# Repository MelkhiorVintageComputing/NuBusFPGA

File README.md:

# A FPGA on a NuBus card...

## Goal

The goal of this repository is to be able to interface a modern (2021 era) [FPGA](https://en.wikipedia.org/wiki/Field-programmable_gate_array) with a [NuBus](https://en.wikipedia.org/wiki/NuBus) host, specifically Apple's [Macintosh II](https://en.wikipedia.org/wiki/Macintosh_II_family) and [Macintosh Quadra](https://en.wikipedia.org/wiki/Macintosh_Quadra). NuBus was widely used by Apple and a little by others (such as NeXT), but was progressively displaced by PCI from the mid-90s onward, and is thoroughly obsolete.

So unless you're a retrocomputing enthusiast with such a machine, this is useless. If you are such an enthusiast, then maybe the ability to connect a modern LCD monitor using a digital interface to an old Macintosh might be of interest to you.

This project was 'spun off' the [SBusFPGA](https://github.com/rdolbeau/SBusFPGA), a similar project for the SBus used in Sun's SPARCstation.

## Current status

First prototype is working in a Quadra 650, running MacOS 8.1. It implements a single-screen-resolution, windowboxed multi-resolution, depth-switchable (1/2/4/8/16/32 bits) framebuffer over DVI-in-HDMI-connector (will work with any HDMI-compliant monitor). The framebuffer can be used as secondary/primary/only framebuffer in the machine running OS8.1. Qemu tests indicate this should work with 7.1 & 7.5/7.6 as well. An alternate HDMI PHY also supports audio, enabled as a 8/16 bits, mono/stereo, 44.1 kHz output component in MacOS.

Some basic acceleration now exists for 8/16/32 bits, doing rectangle screen-to-screen blits and pattern rectangle fills. 1/2/4 bits also has some acceleration, but only for byte-aligned cases.

There's also a basic RAM Disk using the 248 MiB of SDRAM not used by the framebuffer. The driver can use either synchronous direct access to the memory by the CPU, or asynchronous using DMA (using 16-bytes blocks). Frustratingly, the direct access methode seems faster.

## The hardware

Directory 'nubus-to-ztex'

The (now obsolete) V1.0 custom board is a NuBus-compliant (I hope...) board, designed to receive a [ZTex USB-FPGA Module 2.13](https://www.ztex.de/usb-fpga-2/usb-fpga-2.13.e.html) as a daughterboard. The ZTex module contains the actual FPGA (Artix-7), some RAM, programming hardware, etc. The NuBus board contains level-shifters & drivers ICs to interface between the NuBus signals and the FPGA, a CPLD handling some level-shifting & the bus mastering arbitration, a serial header, two user Leds, 14 debug Leds tied to specific NuBus or CPLD/FPGA signals, a JTAG header, a USB micro-B connector, a VGA chip & connector, and a HDMI chip & connector. It supports every NuBus feature except the optional parity (i.e. it can do both slave and master modes). The V1.0 board is in commit 3f3371a. The CPLD solution works but is annoying as it requires older Xilinx software (ISE 14.7) and dedicated JTAG programmer to use.

The current board is V1.2. It drops the CPLD and VGA port. Bus arbitration is now done inside the FPGA. It gains a micro-sd slot, and a custom expansion connector that is based (and compatible with, with more signals) PMod. It supports the same accelerated HDMI framebuffer and RAM Disk. Optionally, The Declaration Rom can be stored in a Flash NOR chip connected ot the PMOd expansion connector (easier for working on embedded driver in the DeclRom). The ROM can alternately be stored in a sector of the config flash from the ZTex board on any *FPGA.

The new (July 2023) [ZTex USB-FPGA Module 2.12](https://www.ztex.de/usb-fpga-2/usb-fpga-2.12.e.html) is theoretically compatible with all *FPGA, but at this stage there is some issue when using the 2.12b I own. Some further tests are planned.

The PCBs were designed with Kicad 5.1

## The gateware (Migen)

Directory 'sbus-to-ztex-gateware'

The gateware is written in the Migen language, choosen because that's what [Litex](https://github.com/enjoy-digital/litex/) uses.
It implements a simple CPU-less Litex SoC built around a Wishbone bus, with a custom bridge between the NuBus and the Wishbone.

A Declaration ROM, a SDRAM controller ([litedram](https://github.com/enjoy-digital/litedram) to the on-board DDR3), and the 'Goblin' multi-depth framebuffer can be connected to that bus. Other devices could be added, see the SBusFPGA or the [Common](https://github.com/rdolbeau/VintageBusFPGA_Common) directory, but the software support is missing; vintage System 7/MacOS 8 are not as welcoming to new devices as modern NetBSD. Theoretically, quite a bit of code originally written to support the SBusFPGA in NetBSD/sparc could be reused for similar devices in NetBSD/mac68k, but it has not happened yet.

The SDRAM has its own custom DMA controller, using native Litedram interface to the memory, and some FIFO to/from the NuBus. A custom MacOS driver exposes it as a volatile drive. Driver can use synchronous direct accesses from the CPU (using the NuBus's superslot area), or asynchronous (interrupt-driven) DMA transfers using NuBus 1x block transfers.

## The software

The Declaration ROM is in the subdirectory VintageBusFPGA_Common/DeclROM and includes the driver needed for the unaccelerated framebuffer and the RAM Disk. It needs the [Retro68](https://github.com/autc04/Retro68) toolchain to build.

The code for the NuBusFPGAInit (which should be renamed and enables acceleration) is in NuBusFPGAInit/, and will need a CodeWarrior INIT project to build, on a real Macintosh or an emulated one using e.g. Qemu. It enables graphic acceleration.

The code for the Audio component (which enables audio support over HDMI when using the alternate PHY) is in NuBusFPGAHDMIAudio/.

## FAQ

* Can the framebuffer change resolution ?
 Yes and no. The gateware has a default resolution baked into it that the device will use by default, and can use one of two different physical interface (PHY): the Litex-derived one (which uses DVI signalling) or a more HDMI-like one in verilog. "windowboxed" mode is always availeble, where a smaller esolution is displayed in the middle of the larger screen, which you can select in System 7/MacOS 8 with the Monitor control panel. When using the Litex PHY, some resolution are also available as "hardware" resolution, outputing the appropriate signalling - but the Litex PHY doesn't support audio. The alternate PHY does support audio, but doesn't allow to use a different output resolution, only Full HD (1920x1080) and does support audio output.

* Is Audio supported ?
 Yes and no. a 8 or 16-bits, audio or stereo, 44.1 KHz audio device is available but nly when using the alternate HDMI PHY (see previous question)

* Is USB supported ?
 No. There is a USB connector, but it is currently useless. The gateware could include a USB OHCI host device, and that is supported in the SBusFPGA under NetBSD. However, no Apple OS running on a 68k Mac has any support for USB, so it would require an entire USB stack to be ported, which is a huge undertaking. Also, NuBus is quite a slow bus even by early 2000s standard, and USB OHCI does a lot of DMA all the time, which would use up most if not all (or maybe more than all!) the available bandwidth. There might be some support in NetBSD/mac68k eventually just to test feasibility, but it even there it's unlikely to be useful.

* Is micro-sd supported ?
 Not yet. Hopefully at some point the micro-sd card will be usable as permanent storage in System 7/MacOS 8, but so far it's not working.

* Where is the ROM stored ?
 By default the Declaration ROM is stored inside the FPGA bitstream, so the bitstream must be regenerated for every ROM change. It is possible to store it in a [SPI](https://en.wikipedia.org/wiki/Serial_Peripheral_Interface) Flash NOR chip instead, connected via the expansion connector ([PMod](https://digilent.com/reference/pmod/start)-like) at the back of the NuBusFPGA. My own PMod featuring a SPI Flash NOR and an I2C temperature monitoris available in the [VintageBusFPGA_Common](https://github.com/rdolbeau/VintageBusFPGA_Common) repository, along with an adapter board to program the SPI FLash NOR through the SPI interface of a Raspberry Pi and [flashrom](https://www.flashrom.org/Flashrom).

* Is I2C supported ?
 No. Like USB, I2C doesn't have support in System 7/MacOS 8. It's a lot simpler than USB though. Reading values from a lm75-compatible temperature monitor from System 7/MacOS 8 might be doable, but isn't currently planned. Support for NetBSD/mac68k should be reasonably easy to add as it's already supported in NetBSD/sparc for the SBusFPGA, and unlike USB there's no issue with bandwidth-hungry DMA.

* How about adding Ethernet ?
 Software is the issue. Ethernet is supported by the gateware infrastructure, and a prototype design to add Fast Ethernet via RMII through the expansion connector is available. However, there is currently no software support for it. There's some documentation from Apple, and there's [an example driver available](http://www.mactcp.org.nz/ethernet.html), but the System 7/MacOS 8 driver for LiteEth is still to be written.
 The [SEthernet](https://github.com/rhalkyard/SEthernet) project is a much more likely source of Ethernet for '030-based system.

* Why slow NuBus, when PDS is so much faster ?
 NuBus is well documented, and electrically quite isolated from the rest of the machine. Safer to play with than PDS which is directly connected to the CPU. And the connector for it it still in general use and easy to get. And NuBus is available on multiple generations of machines.
 My primary machine for this is a Quadra 650, with a 68040 and the associated PDS. Unfortunately, the connector for that PDS is near impossible to get nowadadays ([specifications are there](https://tinkerdifferent.com/resources/specifications-for-the-quadra-pds-connector.124/)). '030 PDS uses 120-pins DIN 41612, similar to bur larger than NuBus' 96-pins. They are also available, but less common. But there is a catch - although sharing a connector board-side, the IIsi, SE/30 and IIfx pinouts are slightly different. And the LCIII is completely different.
 Also - see [IIsiFPGA](https://github.com/rdolbeau/IIsiFPGA) and [QuadraFPGA](https://github.com/rdolbeau/QuadraFPGA) :-)

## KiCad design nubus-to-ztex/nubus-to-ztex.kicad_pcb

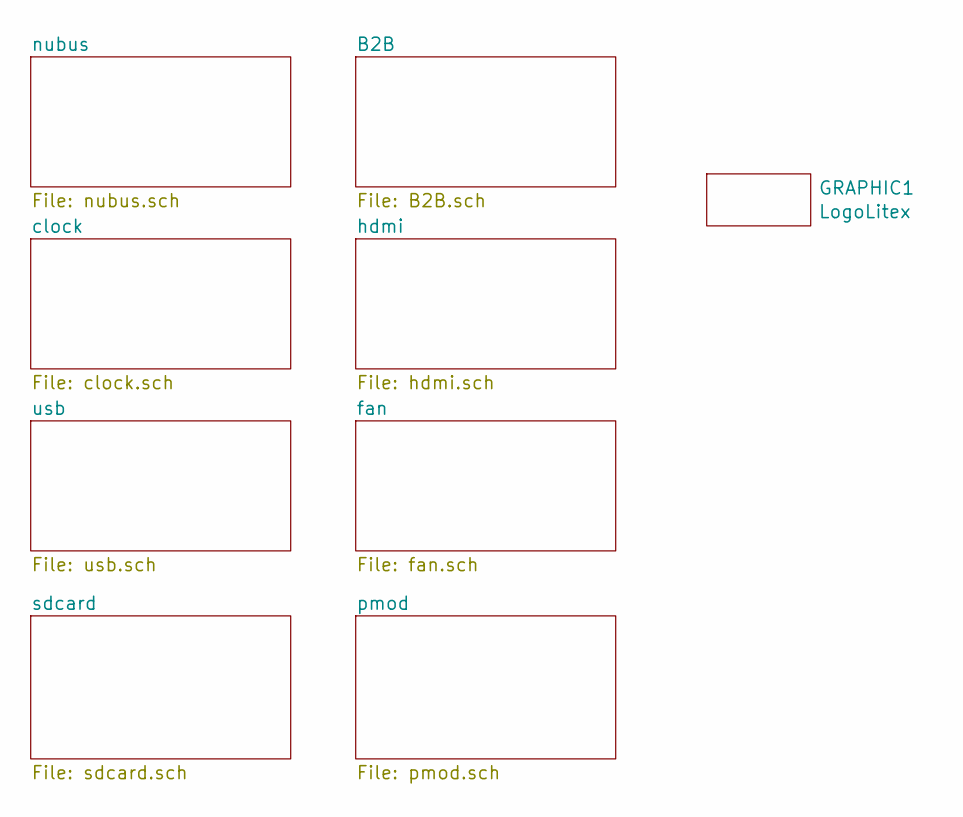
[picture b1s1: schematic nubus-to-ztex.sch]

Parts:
GRAPHIC1: LogoLitex; litex_logo

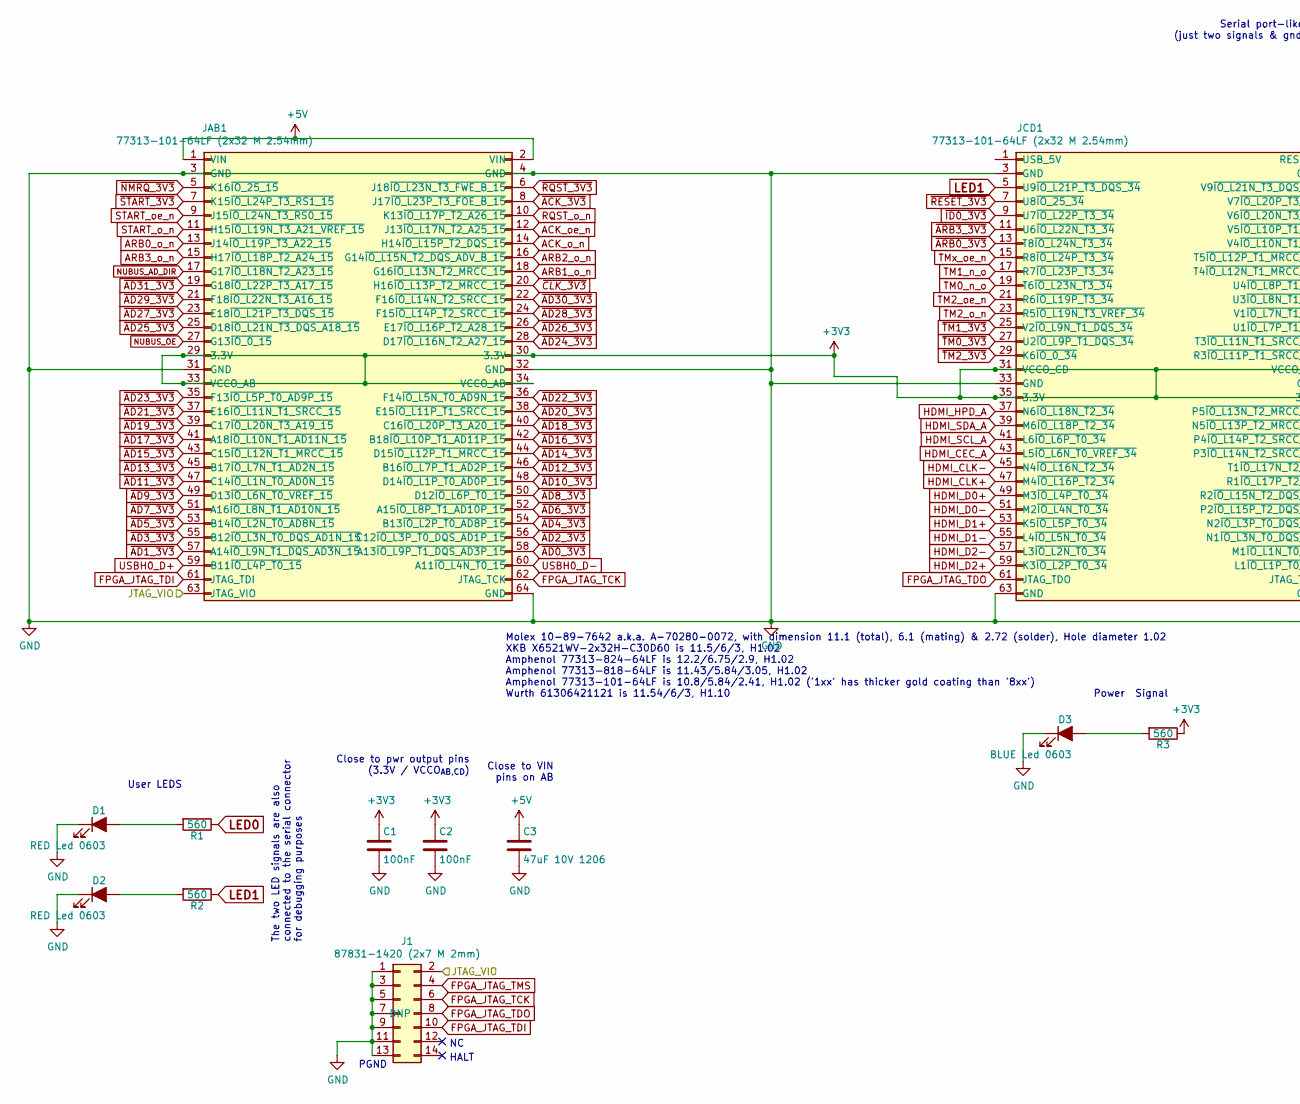
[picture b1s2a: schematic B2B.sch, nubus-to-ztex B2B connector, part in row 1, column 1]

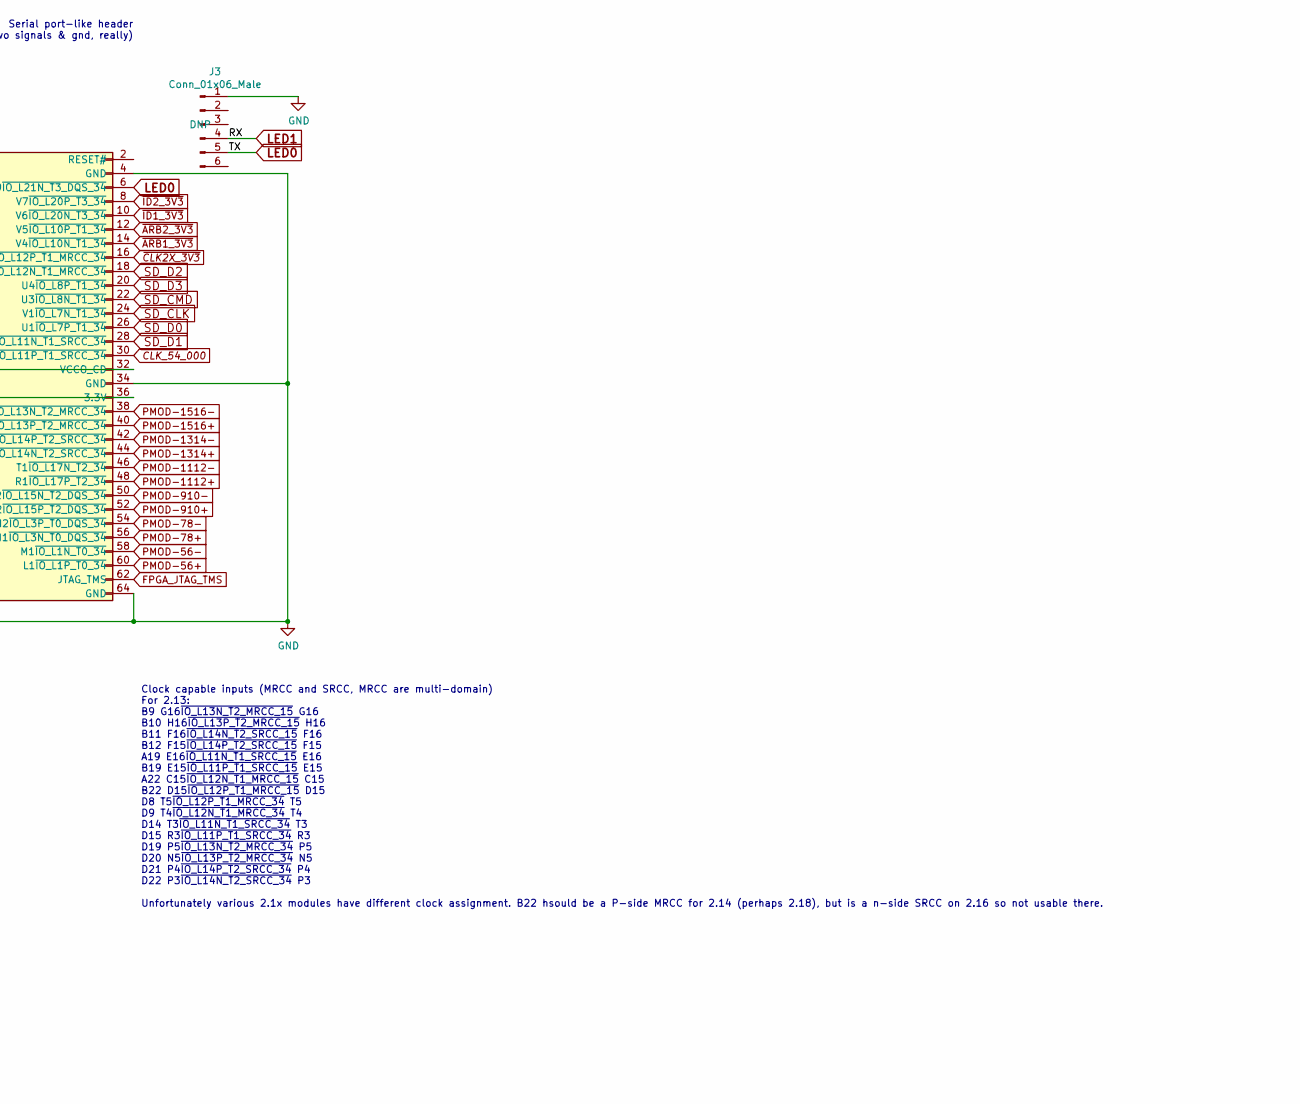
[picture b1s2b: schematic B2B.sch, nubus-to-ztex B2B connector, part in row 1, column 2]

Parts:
C1, C2: 100nF; C_0603_1608Metric; MPN CC0603KRX7R9BB104; Mouser 603-CC603KRX7R8BB104
C3: 47uF 10V 1206; C_1206_3216Metric; MPN-ALT C2012X5R1A476MTJ00E
D1, D2: RED Led 0603; LED_0603_1608Metric; MPN KT-0603R
D3: BLUE Led 0603; LED_0603_1608Metric; MPN 19-217/BHC-ZL1M2RY/3T
J1: 87831-1420 (2x7 M 2mm); PinHeader_2x07_P2.00mm_Vertical_For_SeeedStudio; MPN 87831-1420
J3: Conn_01x06_Male; PinHeader_1x06_P2.54mm_Horizontal_For_SeeedStudio
JAB1: 77313-101-64LF (2x32 M 2.54mm); PinHeader_2x32_P2.54mm_Vertical_For_SeeedStudio; MPN (Molex) 10-89-7642
JCD1: 77313-101-64LF (2x32 M 2.54mm); PinHeader_2x32_P2.54mm_Vertical_For_SeeedStudio; MPN (Molex) 10-89-7642
R1, R2, R3: 560; R_0603_1608Metric; MPN 0603WAF5600T5E

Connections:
+3V3: C1.1, C2.1, JAB1.29 (3.3V), JAB1.30 (3.3V), JAB1.33 (VCCO_AB), JAB1.34 (VCCO_AB), JCD1.31 (VCCO_CD), JCD1.32 (VCCO_CD), JCD1.35 (3.3V), JCD1.36 (3.3V), R3.1; also elsewhere on the board
+5V: C3.1, JAB1.1 (VIN), JAB1.2 (VIN); also elsewhere on the board
/B2B/JTAG_VIO: J1.2, JAB1.63 (JTAG_VIO)
ACK_o_n: JAB1.14 (H14~IO_L15P_T2_DQS_15); also elsewhere on the board
ACK_oe_n: JAB1.12 (J13~IO_L17N_T2_A25_15); also elsewhere on the board
ARB0_o_n: JAB1.13 (J14~IO_L19P_T3_A22_15); also elsewhere on the board
ARB1_o_n: JAB1.18 (G16~IO_L13N_T2_MRCC_15); also elsewhere on the board
ARB2_o_n: JAB1.16 (G14~IO_L15N_T2_DQS_ADV_B_15); also elsewhere on the board
ARB3_o_n: JAB1.15 (H17~IO_L18P_T2_A24_15); also elsewhere on the board
CLK_54_000: JCD1.30 (R3~IO_L11P_T1_SRCC_34); also elsewhere on the board
FPGA_JTAG_TCK: J1.6, JAB1.62 (JTAG_TCK)
FPGA_JTAG_TDI: J1.10, JAB1.61 (JTAG_TDI)
FPGA_JTAG_TDO: J1.8, JCD1.61 (JTAG_TDO)
FPGA_JTAG_TMS: J1.4, JCD1.62 (JTAG_TMS)
GND: C1.2, C2.2, C3.2, D1.1 (K), D2.1 (K), D3.1 (K), J1.1, J1.3, J1.5, J1.7, J1.9, J1.11, J1.13, J3.1, JAB1.3 (GND), JAB1.4 (GND), JAB1.31 (GND), JAB1.32 (GND), JAB1.64 (GND), JCD1.3 (GND), JCD1.4 (GND), JCD1.33 (GND), JCD1.34 (GND), JCD1.63 (GND), JCD1.64 (GND); also elsewhere on the board
HDMI_CEC_A: JCD1.43 (L5~IO_L6N_T0_VREF_34); also elsewhere on the board
HDMI_CLK+: JCD1.47 (M4~IO_L16P_T2_34); also elsewhere on the board
HDMI_CLK-: JCD1.45 (N4~IO_L16N_T2_34); also elsewhere on the board
HDMI_D0+: JCD1.49 (M3~IO_L4P_T0_34); also elsewhere on the board
HDMI_D0-: JCD1.51 (M2~IO_L4N_T0_34); also elsewhere on the board
HDMI_D1+: JCD1.53 (K5~IO_L5P_T0_34); also elsewhere on the board
HDMI_D1-: JCD1.55 (L4~IO_L5N_T0_34); also elsewhere on the board
HDMI_D2+: JCD1.59 (K3~IO_L2P_T0_34); also elsewhere on the board
HDMI_D2-: JCD1.57 (L3~IO_L2N_T0_34); also elsewhere on the board
HDMI_HPD_A: JCD1.37 (N6~IO_L18N_T2_34); also elsewhere on the board
HDMI_SCL_A: JCD1.41 (L6~IO_L6P_T0_34); also elsewhere on the board
HDMI_SDA_A: JCD1.39 (M6~IO_L18P_T2_34); also elsewhere on the board
LED0: J3.5, JCD1.6 (V9~IO_L21N_T3_DQS_34), R1.1
LED1: J3.4, JCD1.5 (U9~IO_L21P_T3_DQS_34), R2.1
NUBUS_AD_DIR: JAB1.17 (G17~IO_L18N_T2_A23_15); also elsewhere on the board
NUBUS_OE: JAB1.27 (G13~IO_0_15); also elsewhere on the board
unnamed: D1.2 (A), R1.2
unnamed: D2.2 (A), R2.2
unnamed: D3.2 (A), R3.2
PMOD-56+: JCD1.60 (L1~IO_L1P_T0_34); also elsewhere on the board
PMOD-56-: JCD1.58 (M1~IO_L1N_T0_34); also elsewhere on the board
PMOD-78+: JCD1.56 (N1~IO_L3N_T0_DQS_34); also elsewhere on the board
PMOD-78-: JCD1.54 (N2~IO_L3P_T0_DQS_34); also elsewhere on the board
PMOD-910+: JCD1.52 (P2~IO_L15P_T2_DQS_34); also elsewhere on the board
PMOD-910-: JCD1.50 (R2~IO_L15N_T2_DQS_34); also elsewhere on the board
PMOD-1112+: JCD1.48 (R1~IO_L17P_T2_34); also elsewhere on the board
PMOD-1112-: JCD1.46 (T1~IO_L17N_T2_34); also elsewhere on the board
PMOD-1314+: JCD1.44 (P3~IO_L14N_T2_SRCC_34); also elsewhere on the board
PMOD-1314-: JCD1.42 (P4~IO_L14P_T2_SRCC_34); also elsewhere on the board
PMOD-1516+: JCD1.40 (N5~IO_L13P_T2_MRCC_34); also elsewhere on the board
PMOD-1516-: JCD1.38 (P5~IO_L13N_T2_MRCC_34); also elsewhere on the board
RQST_o_n: JAB1.10 (K13~IO_L17P_T2_A26_15); also elsewhere on the board
SD_CLK: JCD1.24 (V1~IO_L7N_T1_34); also elsewhere on the board
SD_CMD: JCD1.22 (U3~IO_L8N_T1_34); also elsewhere on the board
SD_D0: JCD1.26 (U1~IO_L7P_T1_34); also elsewhere on the board
SD_D1: JCD1.28 (T3~IO_L11N_T1_SRCC_34); also elsewhere on the board
SD_D2: JCD1.18 (T4~IO_L12N_T1_MRCC_34); also elsewhere on the board
SD_D3: JCD1.20 (U4~IO_L8P_T1_34); also elsewhere on the board
START_o_n: JAB1.11 (H15~IO_L19N_T3_A21_VREF_15); also elsewhere on the board
START_oe_n: JAB1.9 (J15~IO_L24N_T3_RS0_15); also elsewhere on the board
TM0_n_o: JCD1.19 (T6~IO_L23N_T3_34); also elsewhere on the board
TM1_n_o: JCD1.17 (R7~IO_L23P_T3_34); also elsewhere on the board
TM2_o_n: JCD1.23 (R5~IO_L19N_T3_VREF_34); also elsewhere on the board
TM2_oe_n: JCD1.21 (R6~IO_L19P_T3_34); also elsewhere on the board
TMx_oe_n: JCD1.15 (R8~IO_L24P_T3_34); also elsewhere on the board
USBH0_D+: JAB1.59 (B11~IO_L4P_T0_15); also elsewhere on the board
USBH0_D-: JAB1.60 (A11~IO_L4N_T0_15); also elsewhere on the board
~ACK_3V3: JAB1.8 (J17~IO_L23P_T3_FOE_B_15); also elsewhere on the board
~AD0_3V3: JAB1.58 (A13~IO_L9P_T1_DQS_AD3P_15); also elsewhere on the board
~AD1_3V3: JAB1.57 (A14~IO_L9N_T1_DQS_AD3N_15); also elsewhere on the board
~AD2_3V3: JAB1.56 (C12~IO_L3P_T0_DQS_AD1P_15); also elsewhere on the board
~AD3_3V3: JAB1.55 (B12~IO_L3N_T0_DQS_AD1N_15); also elsewhere on the board
~AD4_3V3: JAB1.54 (B13~IO_L2P_T0_AD8P_15); also elsewhere on the board
~AD5_3V3: JAB1.53 (B14~IO_L2N_T0_AD8N_15); also elsewhere on the board
~AD6_3V3: JAB1.52 (A15~IO_L8P_T1_AD10P_15); also elsewhere on the board
~AD7_3V3: JAB1.51 (A16~IO_L8N_T1_AD10N_15); also elsewhere on the board
~AD8_3V3: JAB1.50 (D12~IO_L6P_T0_15); also elsewhere on the board
~AD9_3V3: JAB1.49 (D13~IO_L6N_T0_VREF_15); also elsewhere on the board
~AD10_3V3: JAB1.48 (D14~IO_L1P_T0_AD0P_15); also elsewhere on the board
~AD11_3V3: JAB1.47 (C14~IO_L1N_T0_AD0N_15); also elsewhere on the board
~AD12_3V3: JAB1.46 (B16~IO_L7P_T1_AD2P_15); also elsewhere on the board
~AD13_3V3: JAB1.45 (B17~IO_L7N_T1_AD2N_15); also elsewhere on the board
~AD14_3V3: JAB1.44 (D15~IO_L12P_T1_MRCC_15); also elsewhere on the board
~AD15_3V3: JAB1.43 (C15~IO_L12N_T1_MRCC_15); also elsewhere on the board
~AD16_3V3: JAB1.42 (B18~IO_L10P_T1_AD11P_15); also elsewhere on the board
~AD17_3V3: JAB1.41 (A18~IO_L10N_T1_AD11N_15); also elsewhere on the board
~AD18_3V3: JAB1.40 (C16~IO_L20P_T3_A20_15); also elsewhere on the board
~AD19_3V3: JAB1.39 (C17~IO_L20N_T3_A19_15); also elsewhere on the board
~AD20_3V3: JAB1.38 (E15~IO_L11P_T1_SRCC_15); also elsewhere on the board
~AD21_3V3: JAB1.37 (E16~IO_L11N_T1_SRCC_15); also elsewhere on the board
~AD22_3V3: JAB1.36 (F14~IO_L5N_T0_AD9N_15); also elsewhere on the board
~AD23_3V3: JAB1.35 (F13~IO_L5P_T0_AD9P_15); also elsewhere on the board
~AD24_3V3: JAB1.28 (D17~IO_L16N_T2_A27_15); also elsewhere on the board
~AD25_3V3: JAB1.25 (D18~IO_L21N_T3_DQS_A18_15); also elsewhere on the board
~AD26_3V3: JAB1.26 (E17~IO_L16P_T2_A28_15); also elsewhere on the board
~AD27_3V3: JAB1.23 (E18~IO_L21P_T3_DQS_15); also elsewhere on the board
~AD28_3V3: JAB1.24 (F15~IO_L14P_T2_SRCC_15); also elsewhere on the board
~AD29_3V3: JAB1.21 (F18~IO_L22N_T3_A16_15); also elsewhere on the board
~AD30_3V3: JAB1.22 (F16~IO_L14N_T2_SRCC_15); also elsewhere on the board
~AD31_3V3: JAB1.19 (G18~IO_L22P_T3_A17_15); also elsewhere on the board
~ARB0_3V3: JCD1.13 (T8~IO_L24N_T3_34); also elsewhere on the board
~ARB1_3V3: JCD1.14 (V4~IO_L10N_T1_34); also elsewhere on the board
~ARB2_3V3: JCD1.12 (V5~IO_L10P_T1_34); also elsewhere on the board
~ARB3_3V3: JCD1.11 (U6~IO_L22N_T3_34); also elsewhere on the board
~CLK2X_3V3: JCD1.16 (T5~IO_L12P_T1_MRCC_34); also elsewhere on the board
~CLK_3V3: JAB1.20 (H16~IO_L13P_T2_MRCC_15); also elsewhere on the board
~ID0_3V3: JCD1.9 (U7~IO_L22P_T3_34); also elsewhere on the board
~ID1_3V3: JCD1.10 (V6~IO_L20N_T3_34); also elsewhere on the board
~ID2_3V3: JCD1.8 (V7~IO_L20P_T3_34); also elsewhere on the board
~NMRQ_3V3: JAB1.5 (K16~IO_25_15); also elsewhere on the board
~RESET_3V3: JCD1.7 (U8~IO_25_34); also elsewhere on the board
~RQST_3V3: JAB1.6 (J18~IO_L23N_T3_FWE_B_15); also elsewhere on the board
~START_3V3: JAB1.7 (K15~IO_L24P_T3_RS1_15); also elsewhere on the board
~TM0_3V3: JCD1.27 (U2~IO_L9P_T1_DQS_34); also elsewhere on the board
~TM1_3V3: JCD1.25 (V2~IO_L9N_T1_DQS_34); also elsewhere on the board
~TM2_3V3: JCD1.29 (K6~IO_0_34); also elsewhere on the board

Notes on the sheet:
Clock capable inputs (MRCC and SRCC, MRCC are multi-domain) For 2.13: B9 G16~IO_L13N_T2_MRCC_15 G16 B10 H16~IO_L13P_T2_MRCC_15 H16 B11 F16~IO_L14N_T2_SRCC_15 F16 B12 F15~IO_L14P_T2_SRCC_15 F15 A19 E16~IO_L11N_T1_SRCC_15 E16 B19 E15~IO_L11P_T1_SRCC_15 E15 A22 C15~IO_L12N_T1_MRCC_15 C15 B22 D15~IO_L1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
PGND
HALT
User LEDS
Power Signal
Close to pwr output pins (3.3V / VCCO_{AB,CD})
Serial port-like header (just two signals & gnd, really)
Close to VIN pins on AB
Molex 10-89-7642 a.k.a. A-70280-0072, with dimension 11.1 (total), 6.1 (mating) & 2.72 (solder), Hole diameter 1.02 XKB X6521WV-2x32H-C30D60 is 11.5/6/3, H1.02 Amphenol 77313-824-64LF is 12.2/6.75/2.9, H1.02 Amphenol 77313-818-64LF is 11.43/5.84/3.05, H1.02 Amphenol 77313-101-64LF is 10.8/5.84/2.41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
The two LED signals are also connected to the serial connector for debugging purposes

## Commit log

2021-12-21 push to github
2021-12-21 typos
2022-01-09 large update
2022-01-09 another update after discussion on tinkerdifferent
2022-01-09 Switch from 5V 74FCT245 to 3.3V 74LVT245
2022-01-15 large clean-up update
2022-01-29 more updates
2022-02-05 some missing stuff, minor HW update, SW
2022-04-17 update to first tested version
2022-04-17 new picture
2022-04-18 try for 1/8 bpp support in rom/drvr
2022-04-18 1/2/4/8 bit support
2022-04-18 32-bits 'mllions of colors'
2022-04-19 C secondary, add rsrc directory w/o assembly
2022-04-22 add 16-bits/thousands of colors
2022-05-15 Update memory map ; preliminary accel stuff to test (CW project missing, code resource INIT id 0 with the sysheap flag)
2022-05-16 struct-based access to stack
2022-05-16 preliminary support for pattern-to-screen, reusing single-byte rectfill
2022-05-30 buffers (fifo) write from NuBus to Wishbone, to improve write BW
2022-05-30 pingmaster sort-of-work
2022-06-04 DMA debug with XiBus NuBus & add alternate Migen implementation of NuBus
2022-06-04 add a byte-reversed access mode to accel registers, avoid the byte-reverse on the host
2022-06-04 accel in 16/32 ; includes adding MUL to Vex & fixing a FIFO overrun in NuBus in 32 bits mode
2022-06-04 new interface
2022-06-04 stat module
2022-06-05 Move Vex to a 128-bit Wishbone, and add a bypass to access a dedicated memory port with a 128-bits datapath. Speeds up scrolling quite nicely.
2022-06-05 commit current Vex config
2022-06-06 draft non-synchronous NuBus (using sampling at sysclk to cut down on latency), minimalist support for 1/2/4 accel
2022-06-07 in _sampling, map whole SDRAm in superslot and use the first 248 Mib as a RAM disk with driver in the DeclRom
2022-06-12 use some custom RLE to initiliaze the RAM disk with a valid HFS FS. Still doesn't mount at boot though.
2022-06-12 update ioRange; it doesn't actually affect the cache, only the MMU which we don't use...
2022-06-24 LD/LDU/SD (64-bits, dual regs) support in Vex + accel ; ramdisk tested in Q650
2022-06-25 HW-acceel big pattern (not sure about alignment...), add basic Icon w/ ShowInitIcon
2022-06-25 better patterns
2022-06-26 detect slot in INIT; detect slot in RAMDsk driver ; auto-mount RAMDDsk
2022-06-26 checking in slot
2022-06-26 upadte README
2022-07-14 fix messed up timing...
2022-07-14 dCtlDevBase might be empty, but dCtlSlot is fine...
2022-07-14 'back'port superslot to non-sampling NuBus interface
2022-07-14 preliminary burst support for DMA
2022-07-23 trying to debug DMA for RAMDsk
2022-07-23 rename blit to blit_goblin
2022-07-24 trying to re-instate SBus compatibility
2022-08-15 typo
2022-08-15 better goblin (+accel) in SBus
2022-08-15 fix biblit bug
2022-08-20 Stuff for exa/composite support in X11 (SBusFPGA only for now)
2022-08-20 reverse byte...
2022-08-21 typos...
2022-08-21 more bugfixes for EXA
2022-08-27 Rounding FMA
2022-08-27 byte-swap the FB (SBus)
2022-09-11 track HW changes
2022-09-17 preliminary windowed resolution (640x480 for the moment)
2022-09-17 automate DeclRom more
2022-09-17 oups, typos for 16/32
2022-09-18 Multi (windoboxed) resolution support
2022-09-18 upd readme
2022-09-18 update on write not change
2022-09-18 video page in WS (not yet HW), but MAcOS never uses that ??? Also add pram support.
2022-09-20 fixes suggested on #mac68k
2022-09-20 missing entries (???)
2022-09-21 disable leds
2022-09-21 sync non-sampling with sampling code
2022-09-21 sampling more configurable
2022-09-21 clean-ups
2022-09-21 'de' reaches the PHY, so add inframe to cover the whole screen and stabilize the windowboxed modes
2022-10-01 drop unused test stuf
2022-10-01 try to get DMA to work in the ramdsk driver
2022-10-05 C-ify iodone, irq
2022-10-05 Remove ASM glue in driver table ; replace asm funciton MyaAddDrive by C version
2022-10-06 pc-relative code from the compiler
2022-10-06 rework build system
2022-10-06 remove primary/secondary asm stubs
2022-10-06 simplify
2022-10-06 oups
2022-10-06 cleanup
2022-10-07 rework Dsk Prime function
2022-10-08 refactor ram dsk driver a bit more, some work toward multiplexed interrupt
2022-10-08 DMA + IRQ for RAM Disk
2022-10-09 named parameters for more compatibility
2022-10-31 Add XiBus as a module
2022-10-31 move to submodules XiBus
2022-10-31 move goblin to common
2022-10-31 move fb_dma, fb_video to common
2022-10-31 more stuff moved to common
2022-10-31 move blit_goblin to common
2022-10-31 move wb_master to common
2022-10-31 update common
2022-11-01 drop moved files
2022-11-01 update submodule
2022-11-01 forgot to commit last attempt at V1.2
2022-11-01 cleanups, alternative MPN for 2x32 headers (TBC)
2022-11-01 drop vga
2022-11-01 more stuff thinking about V1.2
2022-11-01 reinstate some useful debug LEDs
2022-11-01 comments
2022-11-01 unused footprint for testing alternate MPN
2022-11-01 cut down brightness of LEDs, more 2x32 pin headers reference
2022-11-01 update everything
2022-11-01 move shielding to hdmi, trace cleanup
2022-11-01 simplify BoM
2022-11-01 update xdc
2022-11-01 draft integration of CPLD in FPGA - can't have internal tri-state signals...
2022-11-01 fix V1.2 TB
2022-11-01 arbiter source file needed
2022-11-01 renames files to V1_2
2022-11-01 renames
2022-11-01 support both version for now
2022-11-04 commit patch for newer Litex
2022-11-05 missing lib
2022-11-05 relative lib
2022-11-12 more update to V1.2 to try to limit cost
2022-11-12 more JTAG from TH to SMD
2022-11-12 full BOM
2022-11-12 rounded cutouts...
2022-11-13 more THT->SMT, lexx expensive parts/assembly (?)
2022-11-18 note on V1.0 vs. V1.2
2022-11-18 minor cleanups
2022-12-01 BoM, power plane, serial back to THT, ...
2022-12-01 Smaller via, greater power/gnd clearance
2022-12-11 get ns816-declrom as a submodule, add auto-buidling of nubus_checksum
2022-12-20 preliminary support for the hdl-util/hdmi contorller as an alternative
2023-01-08 HDMI Audio
2023-01-08 submodule for HDMI-Alt
2023-01-10 8-bits support
2023-01-11 HW mono support
2023-01-12 update satus
2023-01-14 track V1.2 pcb update
2023-01-27 move SDRAM init from HW to SW
2023-01-29 mising file for SW SDRAM Init
2023-03-18 some BoM optimization
2023-03-18 more JLCPCB BoM optimization
2023-03-26 thinking out loud, not relevant to NuBus
2023-03-26 even more JLCPCB BoM optimization
2023-04-02 double checking details
2023-04-04 minor changes in BoM
2023-04-04 more Silk
2023-04-04 add sample CW project in SIT file for audio
2023-04-10 forgotten to push Vex changes
2023-04-10 move Scala file for CG6/Goblin acceleration into Common
2023-04-16 better qemu support, exp. add of Eth
2023-04-16 try to improve use_sampling by sampling synchronously to nubus_clk everything but the clock
2023-04-17 V1.2 bringup
2023-04-24 pictures
2023-04-25 ultra-basic readme
2023-04-29 more notes
2023-05-08 more comments
2023-05-13 cast
2023-09-16 license
2023-09-16 add micro-sd HW support
2023-09-16 commit not-yet-working micro-sd code
2023-10-12 HDMIAudio pick HW info from RSRC
2023-10-14 update, including support for ROM-in-builtin-flash
2023-11-18 move some of board platform stuff to common
2023-11-18 commit mdio stuff, doesn't apeear to work
2023-11-18 start factorizing Mac stuff
2023-11-18 add ram in common
2023-11-18 add goblin to common
2023-12-02 add ref
2023-12-02 drop do file for V1.0
2024-02-17 'alt' hdmi from framebuffer, ROM config from gateware, settable pixel clock for non-alt hdmi
2024-02-17 new ref bistream/rom w/ HW resolution (but no audio)
2024-02-23 drop moved file
2024-02-24 updat e REF
2024-05-18 board-based name

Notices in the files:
nubus-to-ztex-gateware/ztex213_nubus.py:
Copyright (c) 2015 Yann Sionneau <yann.sionneau@gmail.com>
Copyright (c) 2015-2019 Florent Kermarrec <florent@enjoy-digital.fr>
Copyright (c) 2020-2021 Romain Dolbeau <romain@dolbeau.org>
SPDX-License-Identifier: BSD-2-Clause
